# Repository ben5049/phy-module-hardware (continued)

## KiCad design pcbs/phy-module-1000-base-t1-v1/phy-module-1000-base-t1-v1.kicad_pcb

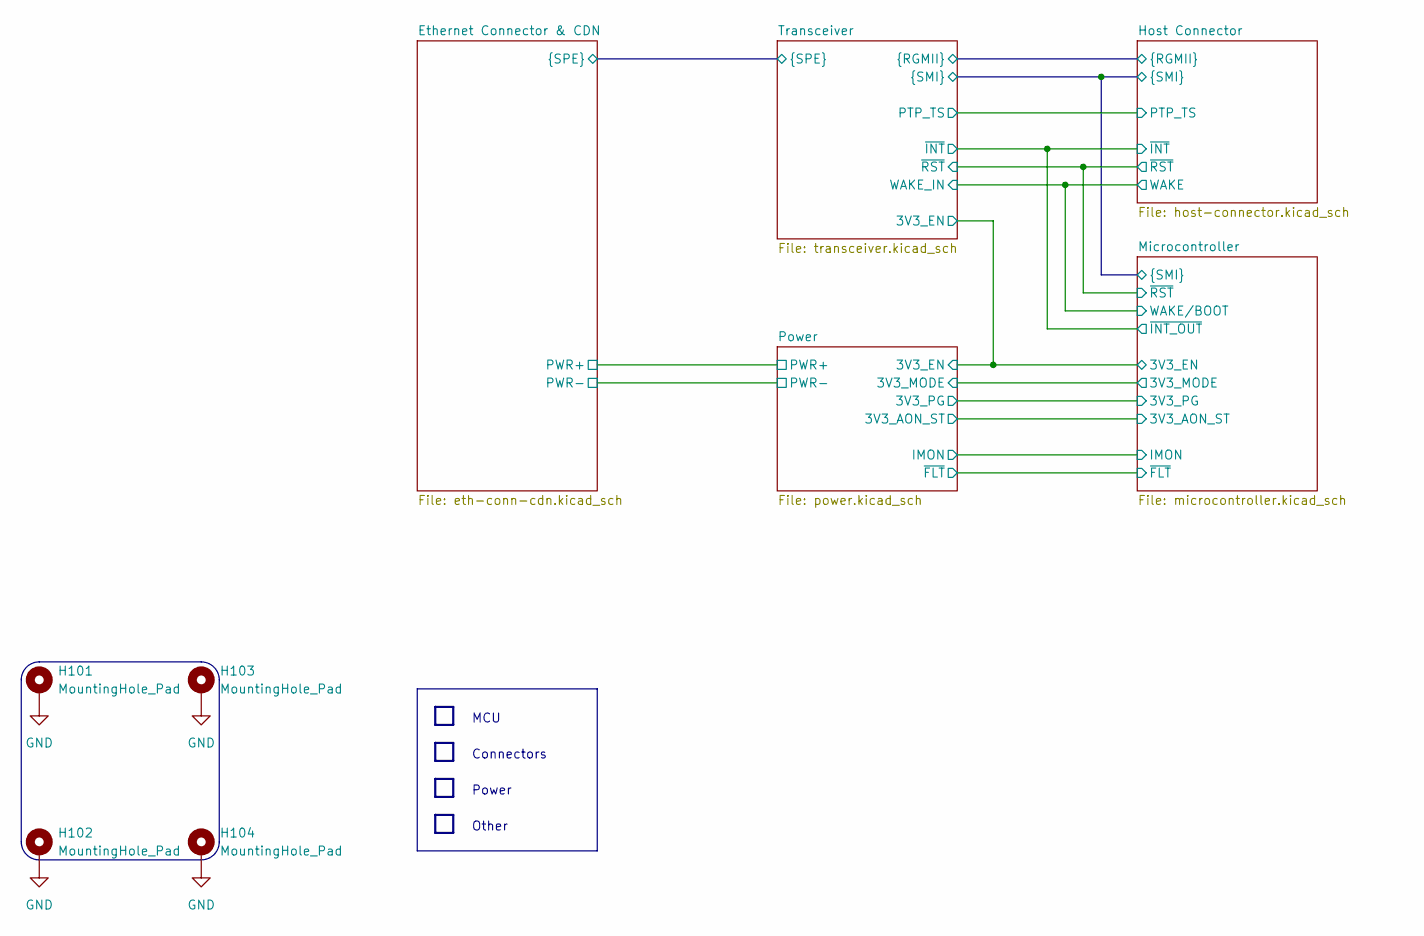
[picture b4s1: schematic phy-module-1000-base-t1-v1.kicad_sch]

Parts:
H101, H102, H103, H104: MountingHole_Pad; MountingHole_2.7mm_M2.5_Pad

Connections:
GND: H101.1, H102.1, H103.1, H104.1; also elsewhere on the board

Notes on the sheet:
Other
Connectors
MCU
Power

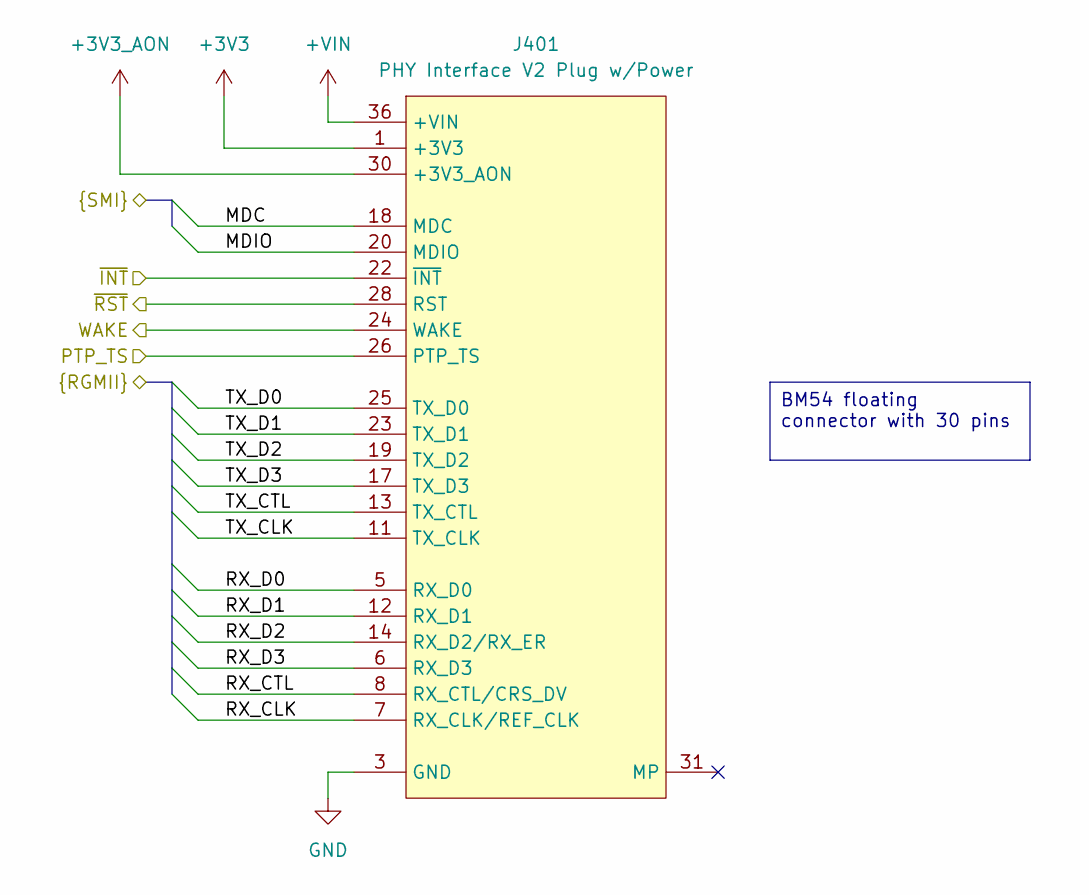
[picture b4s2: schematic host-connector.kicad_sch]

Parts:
J401: PHY Interface V2 Plug w/Power; BM54F3030DP04V51-PWR

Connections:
+3V3: J401.1 (+3V3), J401.2 (+3V3), J401.29 (+3V3); also elsewhere on the board
+3V3_AON: J401.30 (+3V3_AON); also elsewhere on the board
+VIN: J401.36 (+VIN); also elsewhere on the board
/Host Connector/MDC: J401.18 (MDC); also elsewhere on the board
/Host Connector/MDIO: J401.20 (MDIO); also elsewhere on the board
/Host Connector/PTP_TS: J401.26 (PTP_TS); also elsewhere on the board
/Host Connector/RX_CLK: J401.7 (RX_CLK/REF_CLK); also elsewhere on the board
/Host Connector/RX_CTL: J401.8 (RX_CTL/CRS_DV); also elsewhere on the board
/Host Connector/RX_D0: J401.5 (RX_D0); also elsewhere on the board
/Host Connector/RX_D1: J401.12 (RX_D1); also elsewhere on the board
/Host Connector/RX_D2: J401.14 (RX_D2/RX_ER); also elsewhere on the board
/Host Connector/RX_D3: J401.6 (RX_D3); also elsewhere on the board
/Host Connector/TX_CLK: J401.11 (TX_CLK); also elsewhere on the board
/Host Connector/TX_CTL: J401.13 (TX_CTL); also elsewhere on the board
/Host Connector/TX_D0: J401.25 (TX_D0); also elsewhere on the board
/Host Connector/TX_D1: J401.23 (TX_D1); also elsewhere on the board
/Host Connector/TX_D2: J401.19 (TX_D2); also elsewhere on the board
/Host Connector/TX_D3: J401.17 (TX_D3); also elsewhere on the board
/Host Connector/WAKE: J401.24 (WAKE); also elsewhere on the board
/Host Connector/~INT: J401.22 (~INT); also elsewhere on the board
/Host Connector/~RST: J401.28 (RST); also elsewhere on the board
GND: J401.3 (GND), J401.4 (GND), J401.9 (GND), J401.10 (GND), J401.15 (GND), J401.16 (GND), J401.21 (GND), J401.27 (GND), J401.35 (GND); also elsewhere on the board

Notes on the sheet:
BM54 floating connector with 30 pins

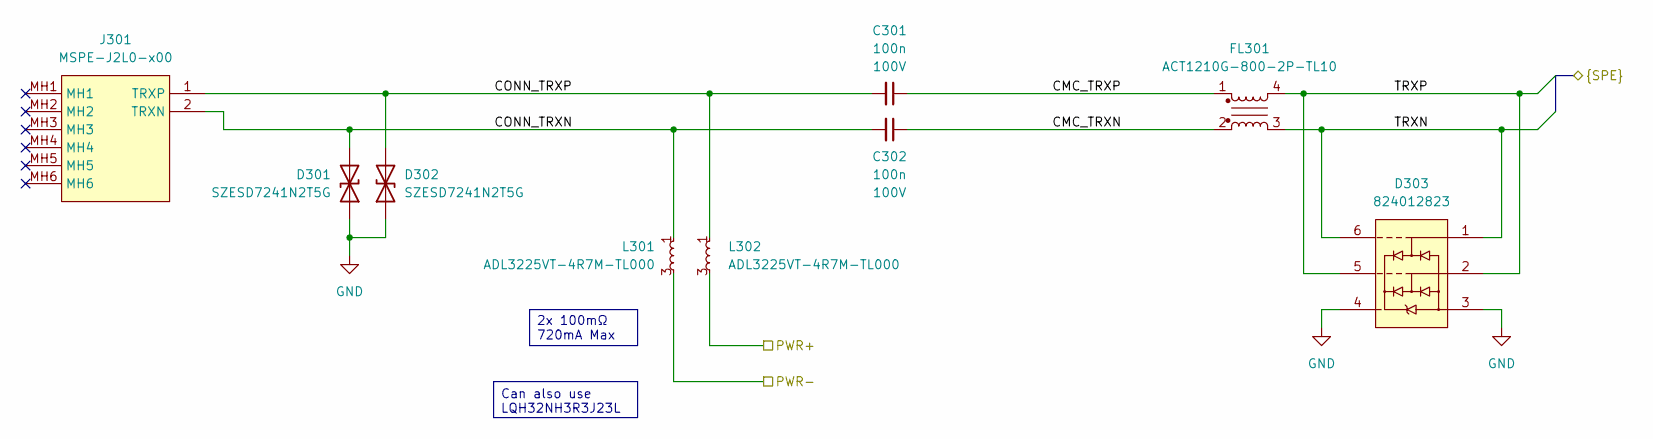
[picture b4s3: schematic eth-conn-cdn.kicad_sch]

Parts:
C301, C302: 100n; C_0603; Voltage 100V
D301, D302: SZESD7241N2T5G; SZESD7462N2T5G; Mouser Part Number 863-SZESD7241N2T5G
D303: 824012823; Mouser Part Number 710-824012823
FL301: ACT1210G-800-2P-TL10; ACT1210G; Mouser Part Number 810-ACT1210G8002PTL1
J301: MSPE-J2L0-x00; MSPEJ2L0x00; Mouser Part Number 523-MSPE-J2L0-B00
L301, L302: ADL3225VT-4R7M-TL000; ADL3225VT4R7MTL000; Mouser Part Number 810-ADL3225VT4R7MTL0

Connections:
/Ethernet Connector & CDN/CMC_TRXN: C302.1, FL301.2
/Ethernet Connector & CDN/CMC_TRXP: C301.1, FL301.1
/Ethernet Connector & CDN/CONN_TRXN: C302.2, D301.2 (A2), J301.2 (TRXN), L301.1, L301.2
/Ethernet Connector & CDN/CONN_TRXP: C301.2, D302.2 (A2), J301.1 (TRXP), L302.1, L302.2
/Ethernet Connector & CDN/PWR+: L302.3, L302.4; also elsewhere on the board
/Ethernet Connector & CDN/PWR-: L301.3, L301.4; also elsewhere on the board
/Ethernet Connector & CDN/TRXN: D303.1, D303.6, FL301.3; also elsewhere on the board
/Ethernet Connector & CDN/TRXP: D303.2, D303.5, FL301.4; also elsewhere on the board
GND: D301.1 (A1), D302.1 (A1), D303.3, D303.4; also elsewhere on the board

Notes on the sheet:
2x 100mΩ 720mA Max
Can also use LQH32NH3R3J23L

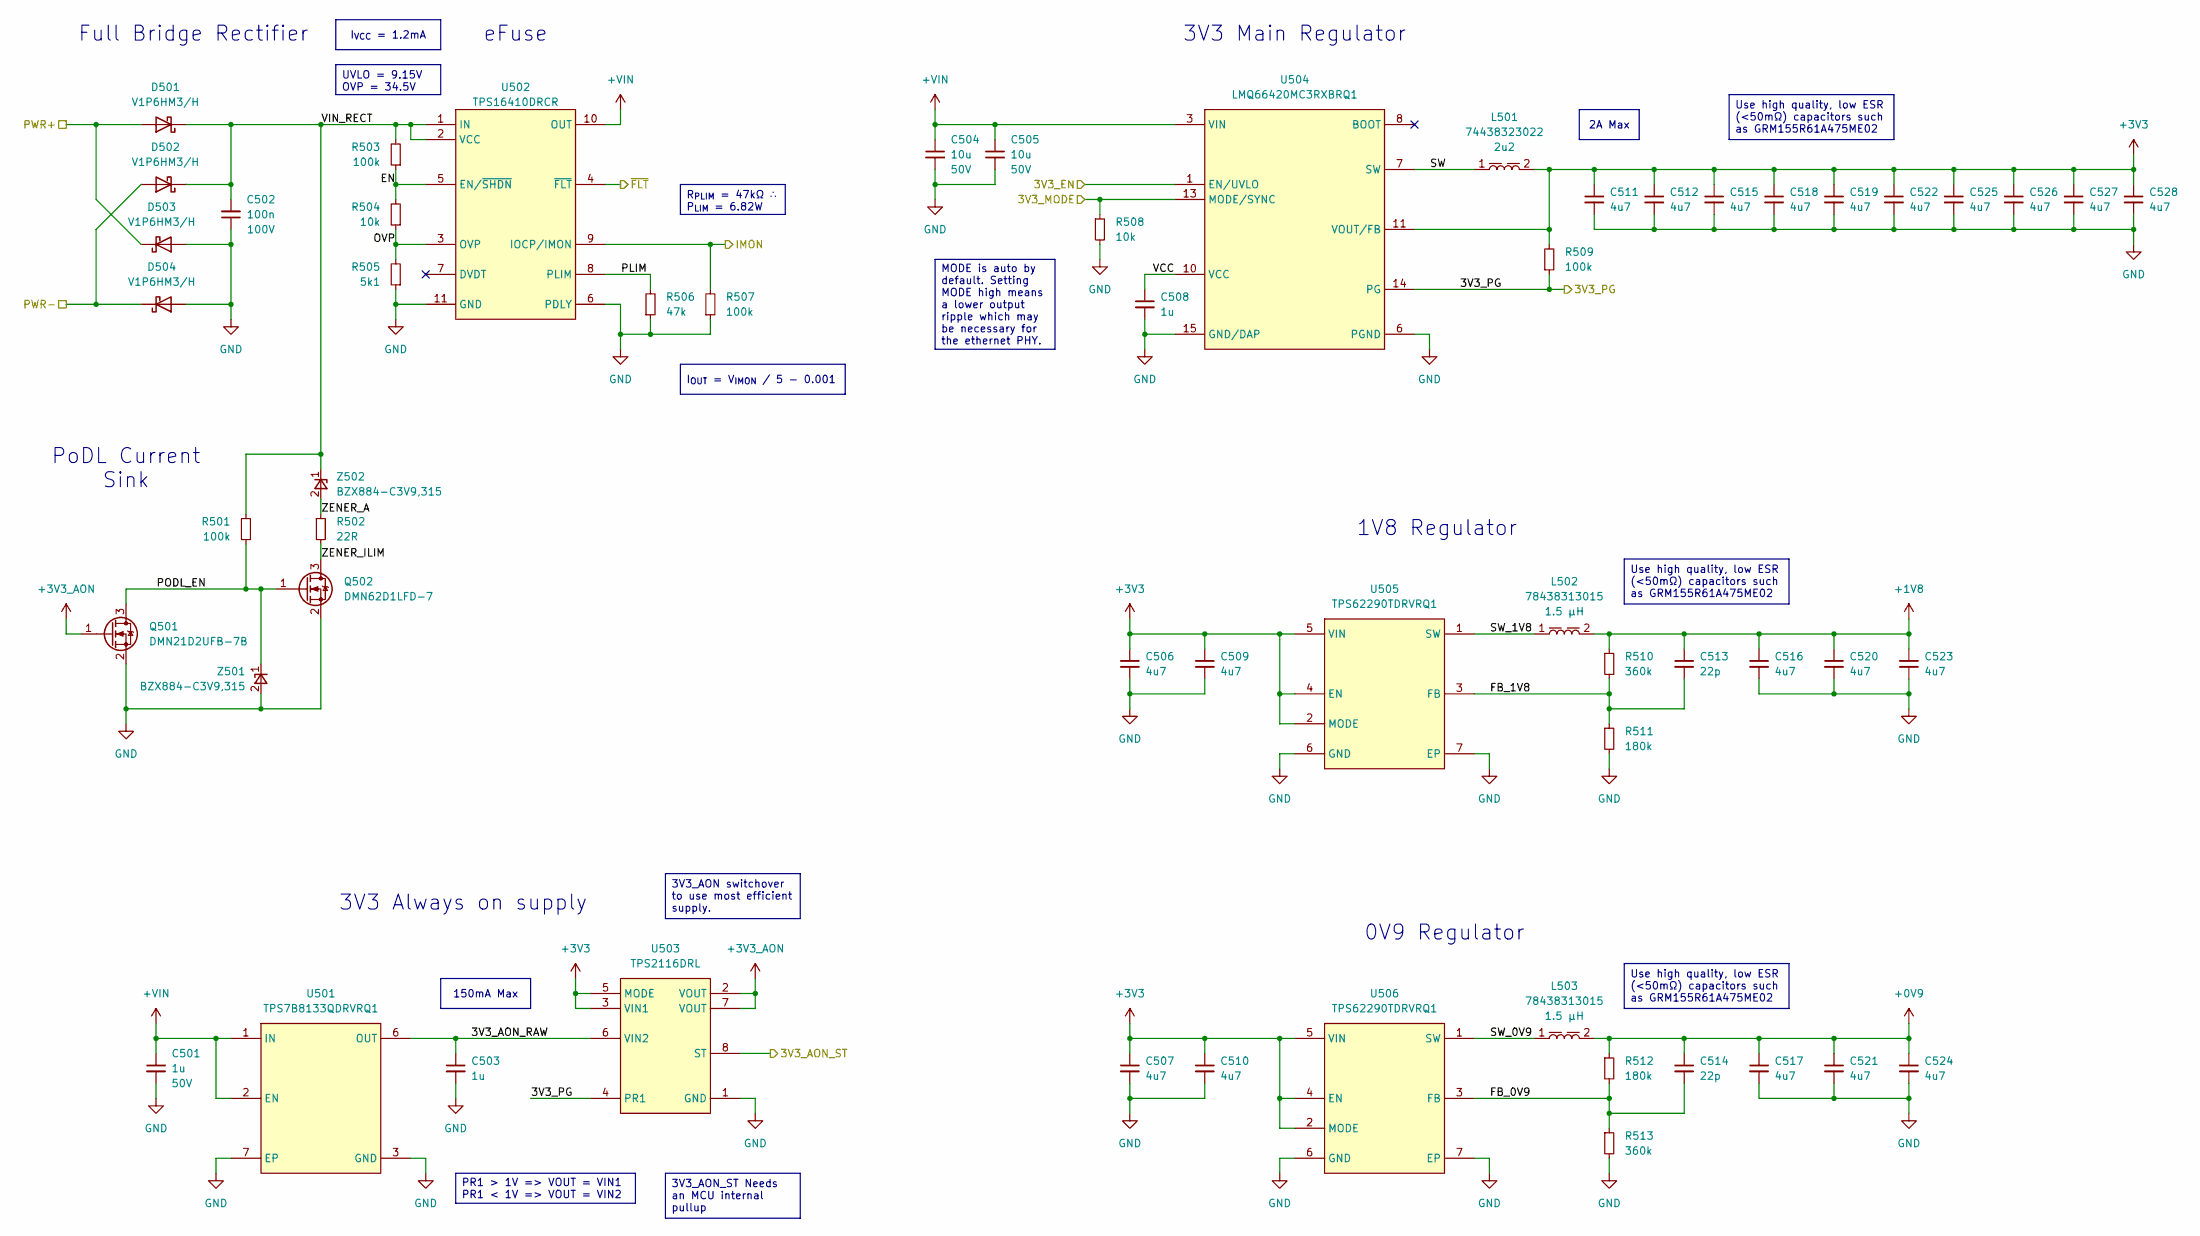
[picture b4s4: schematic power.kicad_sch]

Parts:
C501: 1u; C_0402; Voltage 50V
C502: 100n; C_0402; Voltage 100V
C503, C508: 1u; C_0402
C504, C505: 10u; C_0805; Voltage 50V
C506, C507, C509, C510, C511, C512, C515, C516, C517, C518, C519, C520, C521, C522, C523, C524, C525, C526, C527, C528: 4u7; C_0402
C513, C514: 22p; C_0402
D501, D502, D503, D504: V1P6HM3/H; V1P6HM3_H
L501: 74438323022; L_Wurth_WE-MAPI-2510; Part Number 74438323022
L502, L503: 78438313015; L_Wurth_WE-MAIA-1610; Part Number 78438313015
Q501: DMN21D2UFB-7B; DMN21D2UFB7B; Mouser Part Number 621-DMN21D2UFB-7B
Q502: DMN62D1LFD-7; DMN62D1LFD; Mouser Part Number 621-DMN62D1LFD-7
R501, R503, R507, R509: 100k; R_0402
R502: 22R; R_0402
R504, R508: 10k; R_0402
R505: 5k1; R_0402
R506: 47k; R_0402
R510, R513: 360k; R_0402
R511, R512: 180k; R_0402
U501: TPS7B8133QDRVRQ1; SON65P200X200X80-7N; Mouser Part Number 595-TPS7B8133QDRVRQ1
U502: TPS16410DRCR; Mouser Part Number 595-TPS16410DRCR
U503: TPS2116DRL; SOTFL50P160X60-8N
U504: LMQ66420MC3RXBRQ1; LMQ664x0
U505, U506: TPS62290TDRVRQ1; SON65P200X200X80-7N; Mouser Part Number 595-TPS62290TDRVRQ1
Z501, Z502: BZX884-C3V9,315; BZX884; Mouser Part Number 771-BZX884-C3V9315

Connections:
+0V9: C514.1, C517.1, C521.1, C524.1, L503.2, R512.1; also elsewhere on the board
+1V8: C513.1, C516.1, C520.1, C523.1, L502.2, R510.1; also elsewhere on the board
+3V3: C506.1, C507.1, C509.1, C510.1, C511.1, C512.1, C515.1, C518.1, C519.1, C522.1, C525.1, C526.1, C527.1, C528.1, L501.2, R509.2, U503.3 (VIN1), U503.5 (MODE), U504.11 (VOUT/FB), U505.2 (MODE), U505.4 (EN), U505.5 (VIN), U506.2 (MODE), U506.4 (EN), U506.5 (VIN); also elsewhere on the board
+3V3_AON: Q501.1 (G), U503.2 (VOUT), U503.7 (VOUT); also elsewhere on the board
+VIN: C501.1, C504.1, C505.1, U501.1 (IN), U501.2 (EN), U502.10 (OUT), U504.3 (VIN); also elsewhere on the board
/Ethernet Connector & CDN/PWR+: D501.2 (A), D503.1 (K); also elsewhere on the board
/Ethernet Connector & CDN/PWR-: D502.2 (A), D504.1 (K); also elsewhere on the board
/Microcontroller/3V3_AON_ST: U503.8 (ST); also elsewhere on the board
/Microcontroller/3V3_EN: U504.1 (EN/UVLO); also elsewhere on the board
/Microcontroller/3V3_MODE: R508.1, U504.13 (MODE/SYNC); also elsewhere on the board
/Microcontroller/IMON: R507.2, U502.9 (IOCP/IMON); also elsewhere on the board
/Microcontroller/~FLT: U502.4 (~FLT); also elsewhere on the board
/Power/3V3_AON_RAW: C503.1, U501.6 (OUT), U503.6 (VIN2)
/Power/3V3_PG: R509.1, U503.4 (PR1), U504.14 (PG); also elsewhere on the board
/Power/EN: R503.1, R504.2, U502.5 (EN/~SHDN)
/Power/FB_0V9: C514.2, R512.2, R513.1, U506.3 (FB)
/Power/FB_1V8: C513.2, R510.2, R511.1, U505.3 (FB)
/Power/OVP: R504.1, R505.2, U502.3 (OVP)
/Power/PLIM: R506.2, U502.8 (PLIM)
/Power/PODL_EN: Q501.3 (D), Q502.1 (G), R501.1, Z501.1 (K)
/Power/SW: L501.1, U504.7 (SW)
/Power/SW_0V9: L503.1, U506.1 (SW)
/Power/SW_1V8: L502.1, U505.1 (SW)
/Power/VCC: C508.1, U504.10 (VCC)
/Power/VIN_RECT: C502.2, D501.1 (K), D502.1 (K), R501.2, R503.2, U502.1 (IN), U502.2 (VCC), Z502.1 (K)
/Power/ZENER_A: R502.1, Z502.2 (A)
/Power/ZENER_ILIM: Q502.3 (D), Q502.4 (D), R502.2
GND: C501.2, C502.1, C503.2, C504.2, C505.2, C506.2, C507.2, C508.2, C509.2, C510.2, C511.2, C512.2, C515.2, C516.2, C517.2, C518.2, C519.2, C520.2, C521.2, C522.2, C523.2, C524.2, C525.2, C526.2, C527.2, C528.2, D503.2 (A), D504.2 (A), Q501.2 (S), Q502.2 (S), R505.1, R506.1, R507.1, R508.2, R511.2, R513.2, U501.3 (GND), U501.4 (GND), U501.7 (EP), U502.6 (PDLY), U502.11 (GND), U502.12 (GND), U502.13 (GND), U502.14 (GND), U502.15 (GND), U503.1 (GND), U504.6 (PGND), U504.15 (GND/DAP), U505.6 (GND), U505.7 (EP), U506.6 (GND), U506.7 (EP), Z501.2 (A); also elsewhere on the board

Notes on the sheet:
1V8 Regulator
Full Bridge Rectifier
3V3 Main Regulator
PoDL Current Sink
0V9 Regulator
3V3 Always on supply
eFuse
R_{PLIM} = 47kΩ ∴ P_{LIM} = 6.82W
UVLO = 9.15V OVP = 34.5V
MODE is auto by default. Setting MODE high means a lower output ripple which may be necessary for the ethernet PHY.
PR1 > 1V => VOUT = VIN1 PR1 < 1V => VOUT = VIN2
3V3_AON switchover to use most efficient supply.
2A Max
Use high quality, low ESR (<50mΩ) capacitors such as GRM155R61A475ME02
150mA Max
3V3_AON_ST Needs an MCU internal pullup
I_{VCC} = 1.2mA
I_{OUT} = V_{IMON} / 5 - 0.001

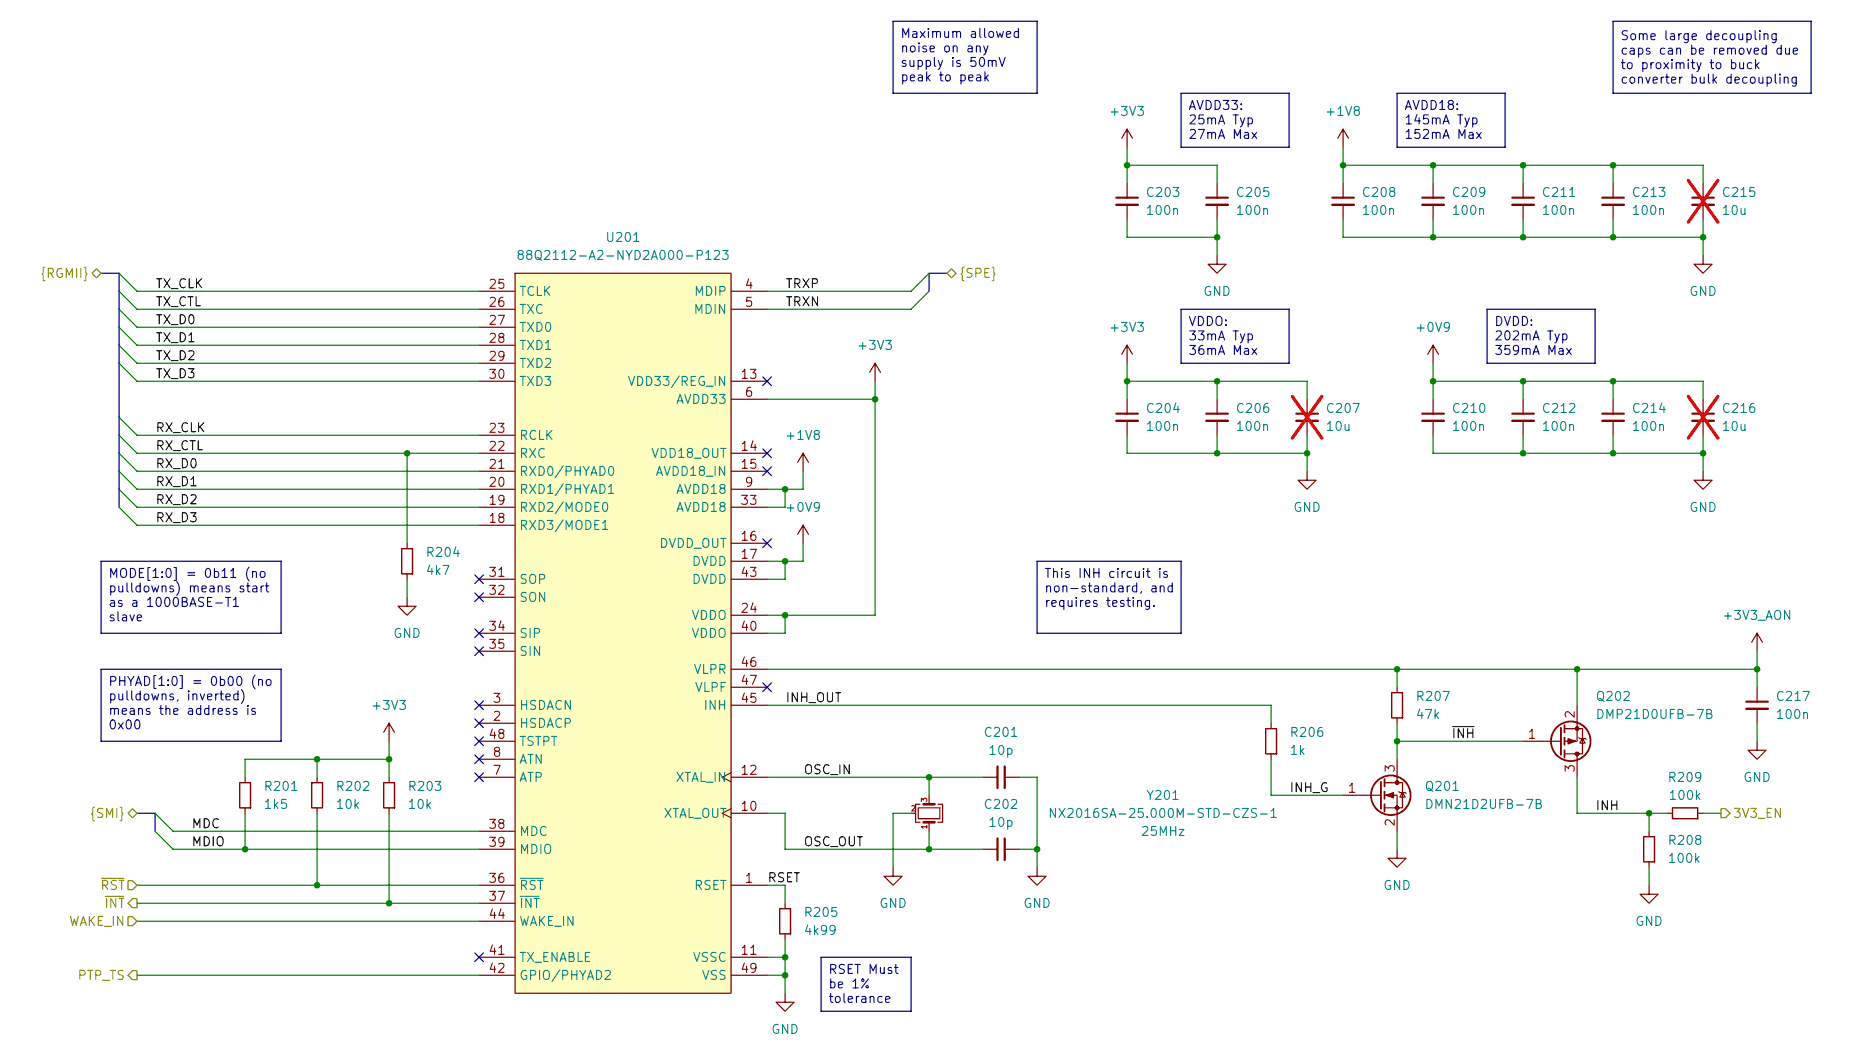
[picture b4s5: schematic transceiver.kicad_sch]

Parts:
C201, C202: 10p; C_0402
C203, C204, C205, C206, C208, C209, C210, C211, C212, C213, C214, C217: 100n; C_0402
C207, C215, C216: 10u; C_0402; not fitted
Q201: DMN21D2UFB-7B; DMN21D2UFB7B; Mouser Part Number 621-DMN21D2UFB-7B
Q202: DMP21D0UFB-7B; DMP21D0UFB7B; Mouser Part Number 621-DMP21D0UFB-7B
R201: 1k5; R_0402
R202, R203: 10k; R_0402
R204: 4k7; R_0402
R205: 4k99; R_0402
R206: 1k; R_0402
R207: 47k; R_0402
R208, R209: 100k; R_0402
U201: 88Q2112-A2-NYD2A000-P123; 88Q2112
Y201: NX2016SA-25.000M-STD-CZS-1; NX2016SA-40M-STD-CZS-3

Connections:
+0V9: C210.1, C212.1, C214.1, C216.1, U201.17 (DVDD), U201.43 (DVDD); also elsewhere on the board
+1V8: C208.1, C209.1, C211.1, C213.1, C215.1, U201.9 (AVDD18), U201.33 (AVDD18); also elsewhere on the board
+3V3: C203.1, C204.1, C205.1, C206.1, C207.1, R201.2, R202.1, R203.2, U201.6 (AVDD33), U201.24 (VDDO), U201.40 (VDDO); also elsewhere on the board
+3V3_AON: C217.1, Q202.2 (S), R207.2, U201.46 (VLPR); also elsewhere on the board
/Ethernet Connector & CDN/TRXN: U201.5 (MDIN); also elsewhere on the board
/Ethernet Connector & CDN/TRXP: U201.4 (MDIP); also elsewhere on the board
/Host Connector/MDC: U201.38 (MDC); also elsewhere on the board
/Host Connector/MDIO: R201.1, U201.39 (MDIO); also elsewhere on the board
/Host Connector/PTP_TS: U201.42 (GPIO/PHYAD2); also elsewhere on the board
/Host Connector/RX_CLK: U201.23 (RCLK); also elsewhere on the board
/Host Connector/RX_CTL: R204.2, U201.22 (RXC); also elsewhere on the board
/Host Connector/RX_D0: U201.21 (RXD0/PHYAD0); also elsewhere on the board
/Host Connector/RX_D1: U201.20 (RXD1/PHYAD1); also elsewhere on the board
/Host Connector/RX_D2: U201.19 (RXD2/MODE0); also elsewhere on the board
/Host Connector/RX_D3: U201.18 (RXD3/MODE1); also elsewhere on the board
/Host Connector/TX_CLK: U201.25 (TCLK); also elsewhere on the board
/Host Connector/TX_CTL: U201.26 (TXC); also elsewhere on the board
/Host Connector/TX_D0: U201.27 (TXD0); also elsewhere on the board
/Host Connector/TX_D1: U201.28 (TXD1); also elsewhere on the board
/Host Connector/TX_D2: U201.29 (TXD2); also elsewhere on the board
/Host Connector/TX_D3: U201.30 (TXD3); also elsewhere on the board
/Host Connector/WAKE: U201.44 (WAKE_IN); also elsewhere on the board
/Host Connector/~INT: R203.1, U201.37 (~INT); also elsewhere on the board
/Host Connector/~RST: R202.2, U201.36 (~RST); also elsewhere on the board
/Microcontroller/3V3_EN: R209.1; also elsewhere on the board
/Transceiver/INH: Q202.3 (D), R208.2, R209.2
/Transceiver/INH_G: Q201.1 (G), R206.1
/Transceiver/INH_OUT: R206.2, U201.45 (INH)
/Transceiver/OSC_IN: C201.2, U201.12 (XTAL_IN), Y201.3
/Transceiver/OSC_OUT: C202.2, U201.10 (XTAL_OUT), Y201.1
/Transceiver/RSET: R205.2, U201.1 (RSET)
/Transceiver/~INH: Q201.3 (D), Q202.1 (G), R207.1
GND: C201.1, C202.1, C203.2, C204.2, C205.2, C206.2, C207.2, C208.2, C209.2, C210.2, C211.2, C212.2, C213.2, C214.2, C215.2, C216.2, C217.2, Q201.2 (S), R204.1, R205.1, R208.1, U201.11 (VSSC), U201.49 (VSS), Y201.2 (G), Y201.4 (G); also elsewhere on the board

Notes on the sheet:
Maximum allowed noise on any supply is 50mV peak to peak
RSET Must be 1% tolerance
This INH circuit is non-standard, and requires testing.
Some large decoupling caps can be removed due to proximity to buck converter bulk decoupling
PHYAD[1:0] = 0b00 (no pulldowns, inverted) means the address is 0x00
DVDD: 202mA Typ 359mA Max
MODE[1:0] = 0b11 (no pulldowns) means start as a 1000BASE-T1 slave
VDDO: 33mA Typ 36mA Max
AVDD33: 25mA Typ 27mA Max
AVDD18: 145mA Typ 152mA Max

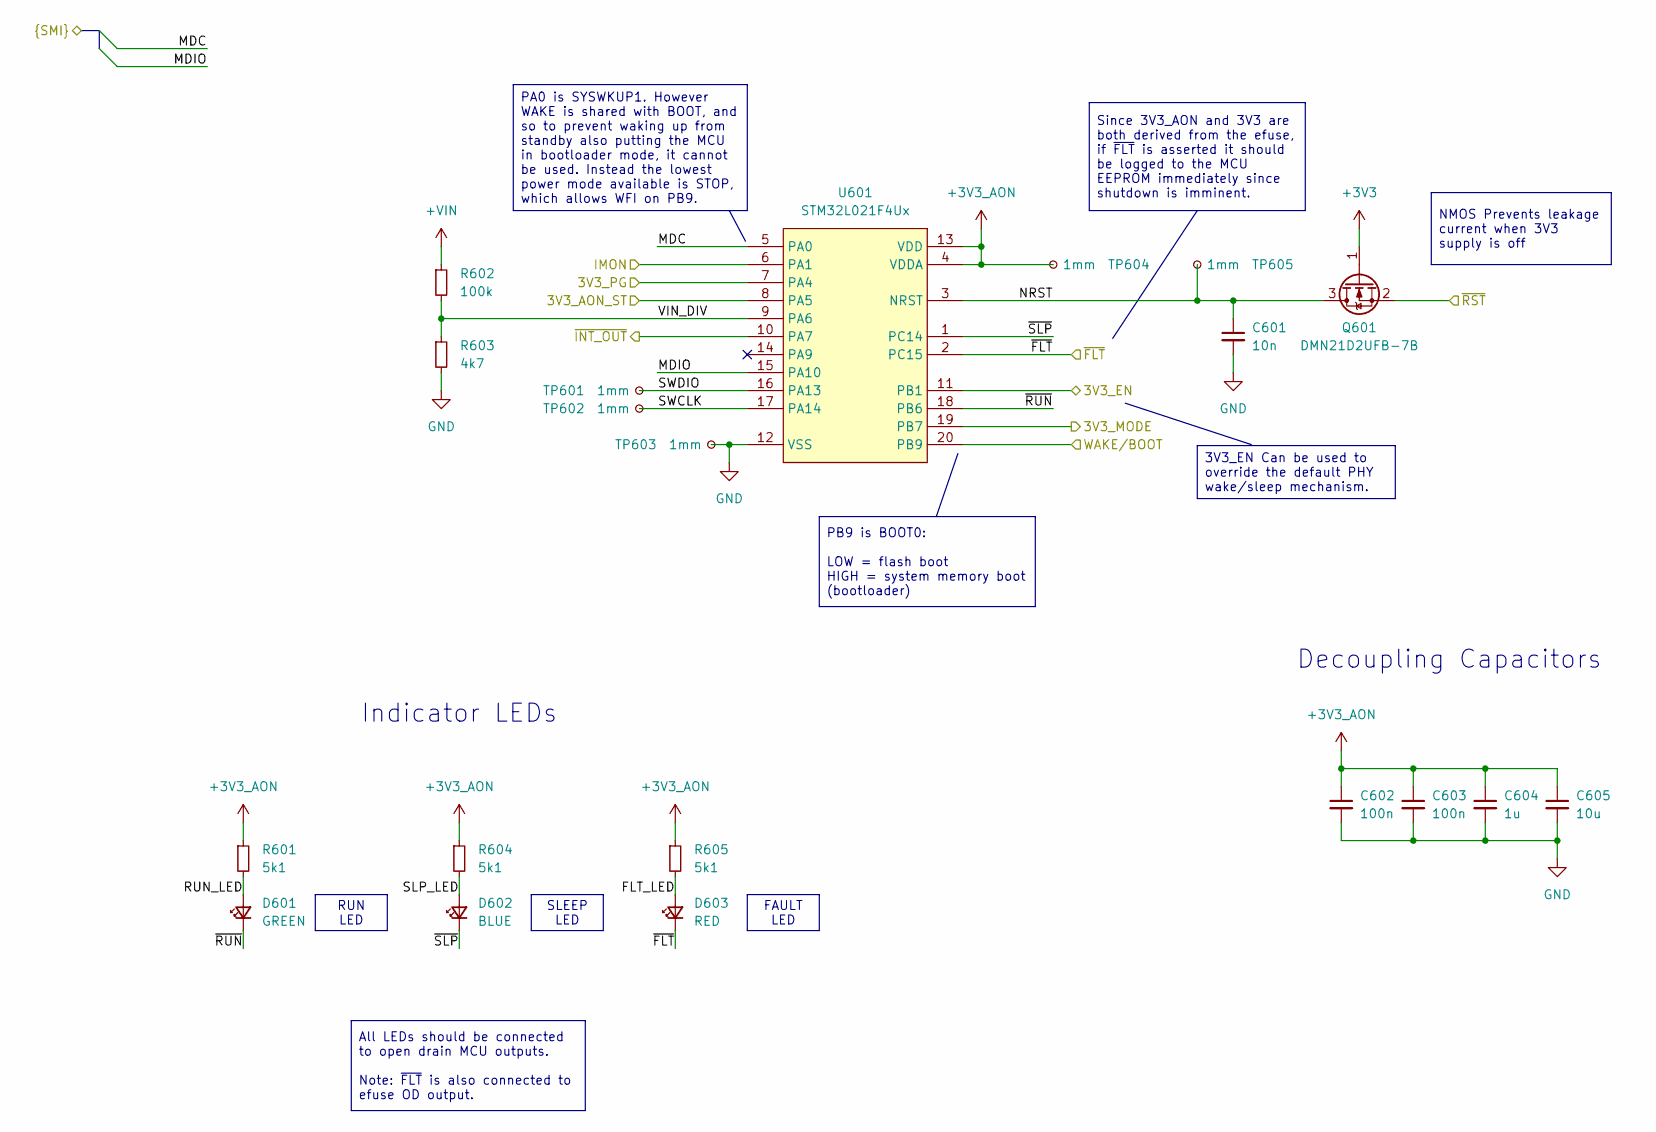
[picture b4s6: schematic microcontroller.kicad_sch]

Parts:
C601: 10n; C_0402
C602, C603: 100n; C_0402
C604: 1u; C_0402
C605: 10u; C_0402
D601: GREEN; LED_0402
D602: BLUE; LED_0402
D603: RED; LED_0402
Q601: DMN21D2UFB-7B; DMN21D2UFB7B; Mouser Part Number 621-DMN21D2UFB-7B
R601, R604, R605: 5k1; R_0402
R602: 100k; R_0402
R603: 4k7; R_0402
TP601, TP602, TP603, TP604, TP605: 1mm; TestPoint_Pad_D1.0mm
U601: STM32L021F4Ux; ST_UFQFPN-20_3x3mm_P0.5mm

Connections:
+3V3: Q601.1 (G); also elsewhere on the board
+3V3_AON: C602.1, C603.1, C604.1, C605.1, R601.1, R604.1, R605.1, TP604.1, U601.4 (VDDA), U601.13 (VDD); also elsewhere on the board
+VIN: R602.1; also elsewhere on the board
/Host Connector/MDC: U601.5 (PA0); also elsewhere on the board
/Host Connector/MDIO: U601.15 (PA10); also elsewhere on the board
/Host Connector/WAKE: U601.20 (PB9); also elsewhere on the board
/Host Connector/~INT: U601.10 (PA7); also elsewhere on the board
/Host Connector/~RST: Q601.2 (S); also elsewhere on the board
/Microcontroller/3V3_AON_ST: U601.8 (PA5); also elsewhere on the board
/Microcontroller/3V3_EN: U601.11 (PB1); also elsewhere on the board
/Microcontroller/3V3_MODE: U601.19 (PB7); also elsewhere on the board
/Microcontroller/FLT_LED: D603.2 (A), R605.2
/Microcontroller/IMON: U601.6 (PA1); also elsewhere on the board
/Microcontroller/NRST: C601.1, Q601.3 (D), TP605.1, U601.3 (NRST)
/Microcontroller/RUN_LED: D601.2 (A), R601.2
/Microcontroller/SLP_LED: D602.2 (A), R604.2
/Microcontroller/SWCLK: TP602.1, U601.17 (PA14)
/Microcontroller/SWDIO: TP601.1, U601.16 (PA13)
/Microcontroller/VIN_DIV: R602.2, R603.1, U601.9 (PA6)
/Microcontroller/~FLT: D603.1 (K), U601.2 (PC15); also elsewhere on the board
/Microcontroller/~RUN: D601.1 (K), U601.18 (PB6)
/Microcontroller/~SLP: D602.1 (K), U601.1 (PC14)
/Power/3V3_PG: U601.7 (PA4); also elsewhere on the board
GND: C601.2, C602.2, C603.2, C604.2, C605.2, R603.2, TP603.1, U601.12 (VSS); also elsewhere on the board

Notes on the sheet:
Decoupling Capacitors
Indicator LEDs
RUN LED
PA0 is SYSWKUP1. However WAKE is shared with BOOT, and so to prevent waking up from standby also putting the MCU in bootloader mode, it cannot be used. Instead the lowest power mode available is STOP, which allows WFI on PB9.
PB9 is BOOT0: LOW = flash boot HIGH = system memory boot (bootloader)
Since 3V3_AON and 3V3 are both derived from the efuse, if ~{FLT} is asserted it should be logged to the MCU EEPROM immediately since shutdown is imminent.
FAULT LED
SLEEP LED
All LEDs should be connected to open drain MCU outputs. Note: ~{FLT} is also connected to efuse OD output.
3V3_EN Can be used to override the default PHY wake/sleep mechanism.
NMOS Prevents leakage current when 3V3 supply is off

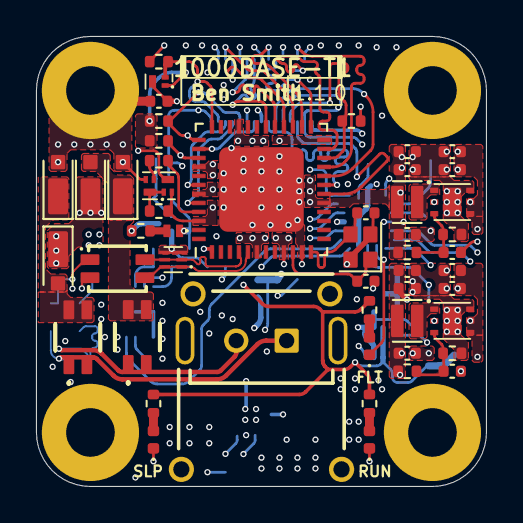
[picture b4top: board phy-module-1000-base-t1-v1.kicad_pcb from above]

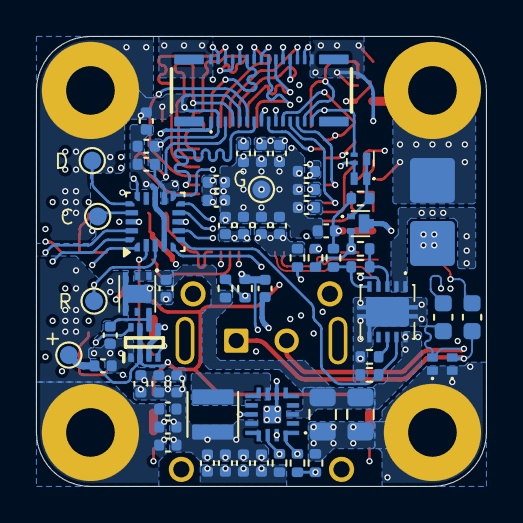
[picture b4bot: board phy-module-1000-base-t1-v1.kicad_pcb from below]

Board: 6 copper layers, 25.0 x 25.0 mm, 119 parts (64 on the bottom side), 68 nets.

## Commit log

2026-03-18 [common] Added 10BASE-T1S & and 1000BASE-T1 PHY Modules
2026-03-19 [10base-t1s] Updated schematic symbols
2026-03-31 [term-10base-t1s] Added files
2026-05-04 [10base-t1s-v1] Added config without PoDL
2026-05-04 [common] Updated gitignore
2026-05-05 [10base-t1s-v1] Updated LED footprints
2026-05-05 [term-10base-t1s] Shrunk to 8mm * 6mm
